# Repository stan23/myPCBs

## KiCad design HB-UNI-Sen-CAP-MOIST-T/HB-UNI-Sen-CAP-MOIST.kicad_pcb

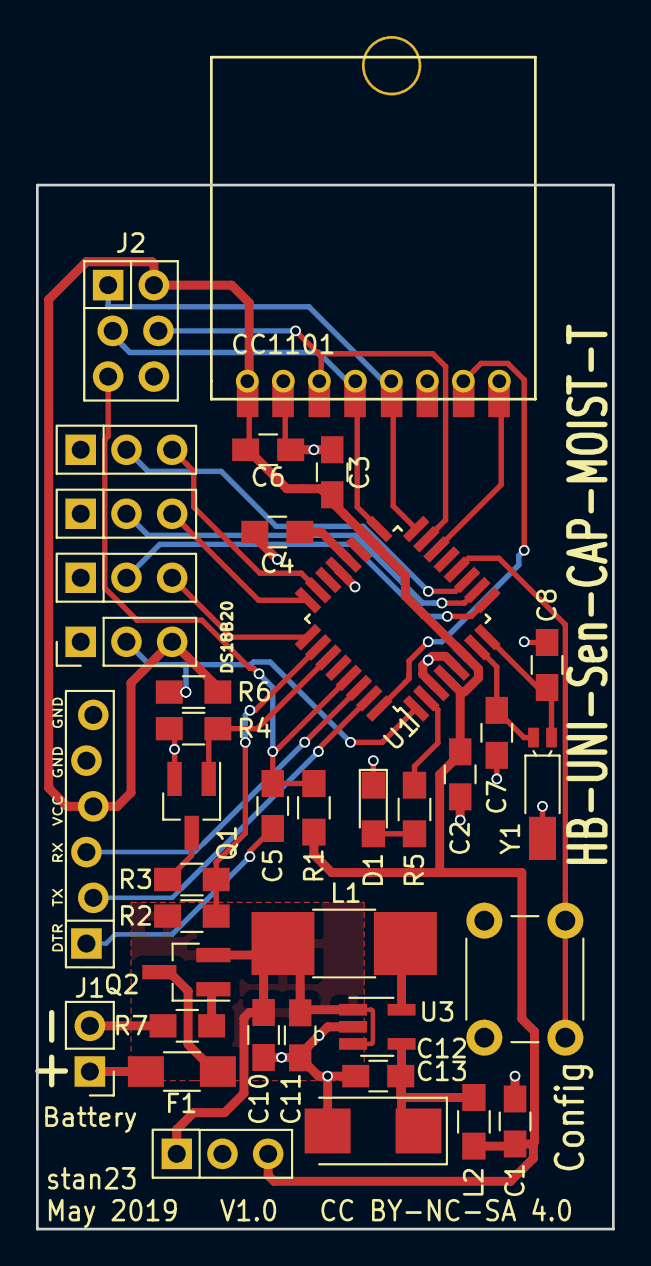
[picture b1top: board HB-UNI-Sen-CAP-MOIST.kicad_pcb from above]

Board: 2 copper layers, 32.0 x 58.0 mm, 38 parts (0 on the bottom side), 33 nets.

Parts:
BT1: Battery; Pin_Header_Straight_1x02_Pitch2.54mm
C1, C10, C12: 10u; C_0805_HandSoldering
C2, C3, C4, C5, C11: 100n; C_0805_HandSoldering
C6: 1u; C_0805_HandSoldering
C7, C8: 12p; C_0805_HandSoldering
C13: 22u; CP_Tantalum_Case-C_EIA-6032-28_Reflow
D1: LED; LED_0805_HandSoldering
F1: PTC 6V/250mA; R_1206_HandSoldering
J1: FTDI; Pin_Header_Straight_1x06_Pitch2.54mm_Tight_Fit
J2: ISP; Pin_Header_Straight_2x03_Pitch2.54mm_Tight_Fit
J3: BL8530; Pin_Header_Straight_1x03_Pitch2.54mm
J11: Sen1; Pin_Header_Straight_1x03_Pitch2.54mm
J12: Sen2; Pin_Header_Straight_1x03_Pitch2.54mm
J13: Sen3; Pin_Header_Straight_1x03_Pitch2.54mm
L1: LQH43CN100K03L; L_1812_HandSoldering
L2: BLM21AG601; L_0805_HandSoldering
Q1: IRLML6344; SOT-23_Handsoldering
Q2: IRLML5203; SOT-23_Handsoldering
R1: 10k; R_0805_HandSoldering
R2: 10/30; R_0805_HandSoldering
R3: 10; R_0805_HandSoldering
R4, R6: 4k7; R_0805_HandSoldering
R5: 1k5; R_0805_HandSoldering
R7: 100k; R_0805_HandSoldering
SW1: Config; SW_PUSH_6mm
U1: ATMEGA328-AU; TQFP-32_7x7mm_Pitch0.8mm_HandSoldering
U2: CC1101; CC1101_Module
U3: MAX1724; SOT-23-5_HandSoldering
U4: DS18B20; Pin_Header_Straight_1x03_Pitch2.54mm
Y1: 32 kiHz; Crystal_SMD_MicroCrystal_MS3V-T1R

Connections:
+BATT: C10.1, C11.1, J3.1, L1.2, Q2.2, R2.1, U3.1, U3.3
/1WIRE: R6.2, U1.1, U4.2
/AREF: C4.1, U1.20
/BAT_MEAS: R2.2, R3.1, U1.26
/BAT_MEAS_EN: Q1.1, R4.1, U1.27
/CONFIG: SW1.1, U1.12
/CS: U1.14, U2.8
/DTR: C5.1, J1.1
/EN1: J11.2, U1.11
/EN2: J12.2, U1.10
/EN3: J13.2, U1.9
/GDO0: U1.32, U2.7
/LED: R5.1, U1.2
/MISO: J2.1, U1.16, U2.5
/MOSI: J2.4, U1.15, U2.3
/RESET: C5.2, J2.5, R1.2, U1.29
/RX: J1.3, U1.30
/SCK: J2.3, U1.17, U2.4
/SENSOR1: J11.3, U1.23
/SENSOR2: J12.3, U1.24
/SENSOR3: J13.3, U1.25
/TX: J1.2, U1.31
/XTAL1: C7.1, U1.7, Y1.1
/XTAL2: C8.1, U1.8, Y1.2
GND: BT1.2, C1.2, C2.2, C3.2, C4.2, C6.2, C7.2, C8.2, C10.2, C11.2, C12.2, C13.2, D1.1, J1.5, J1.6, J2.6, J3.2, J11.1, J12.1, J13.1, Q1.2, R4.2, R7.2, SW1.2, U1.3, U1.5, U1.21, U2.2, U3.2, U4.1, Y1.3
unnamed: BT1.1, F1.2
unnamed: C12.1, C13.1, L2.1, U3.4
unnamed: D1.2, R5.2
unnamed: F1.1, Q2.3
unnamed: L1.1, U3.5
unnamed: Q1.3, R3.2
unnamed: Q2.1, R7.1
VCC: C1.1, C2.1, C3.1, C6.1, J1.4, J2.2, J3.3, L2.2, R1.1, R6.1, U1.4, U1.6, U1.18, U2.1, U4.3

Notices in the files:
HB-UNI-Sen-CAP-MOIST-T/HB-UNI-Sen-CAP-MOIST.kicad_pcb:
May 2019 V1.0 CC BY-NC-SA 4.0
